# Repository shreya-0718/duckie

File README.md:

# duckie!

Hello! Welcome to my first PCB, powered by Solder!

My slack username: @shreyaluu

This is just a little duck keychain whose eyes light up when the button is pressed. It also buzzes, and the "buzz level" is adjustable with the potentiometer!

### Bill of Materials
- 1x PCB
- 1x 3V Battery
- 2x LEDs
- 2x 220 Ohm Resistor
- 1x Battery Holder
- 1x Vibration Motor
- 1x Potentiometer

### Screenshots :)

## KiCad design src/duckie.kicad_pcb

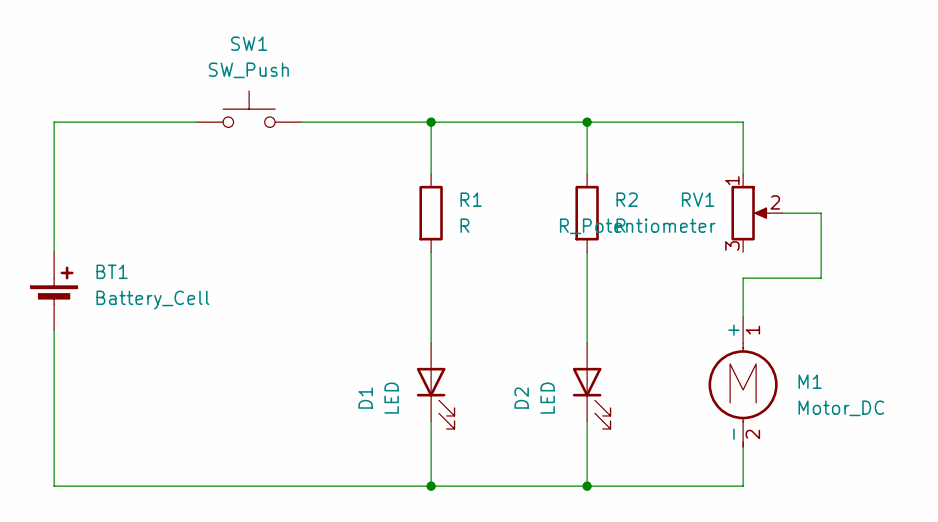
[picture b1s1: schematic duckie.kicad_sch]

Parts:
BT1: Battery_Cell; BatteryHolder_Keystone_3034_1x20mm
D1, D2: LED; LED_D5.0mm
M1: Motor_DC; PinHeader_1x02_P2.54mm_Vertical
R1, R2: R; R_Axial_DIN0207_L6.3mm_D2.5mm_P7.62mm_Horizontal
RV1: R_Potentiometer; Potentiometer_Vishay_T73YP_Vertical
SW1: SW_Push; SW_PUSH_6mm

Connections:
unnamed: BT1.1 (+), SW1.1
unnamed: BT1.2 (-), D1.1 (K), D2.1 (K), M1.2 (-)
unnamed: D1.2 (A), R1.2
unnamed: D2.2 (A), R2.2
unnamed: M1.1 (+), RV1.2
unnamed: R1.1, R2.1, RV1.1, SW1.2

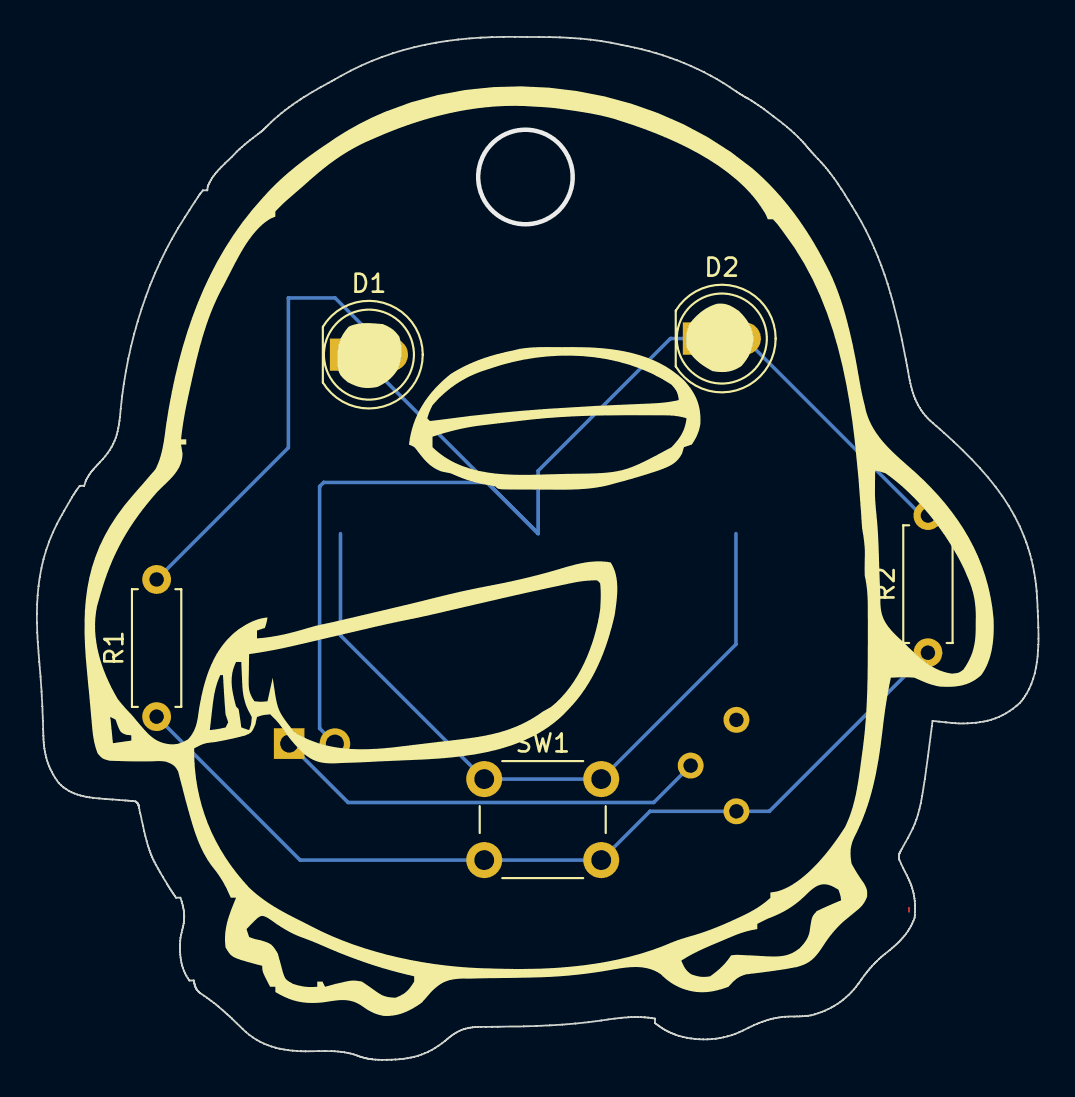
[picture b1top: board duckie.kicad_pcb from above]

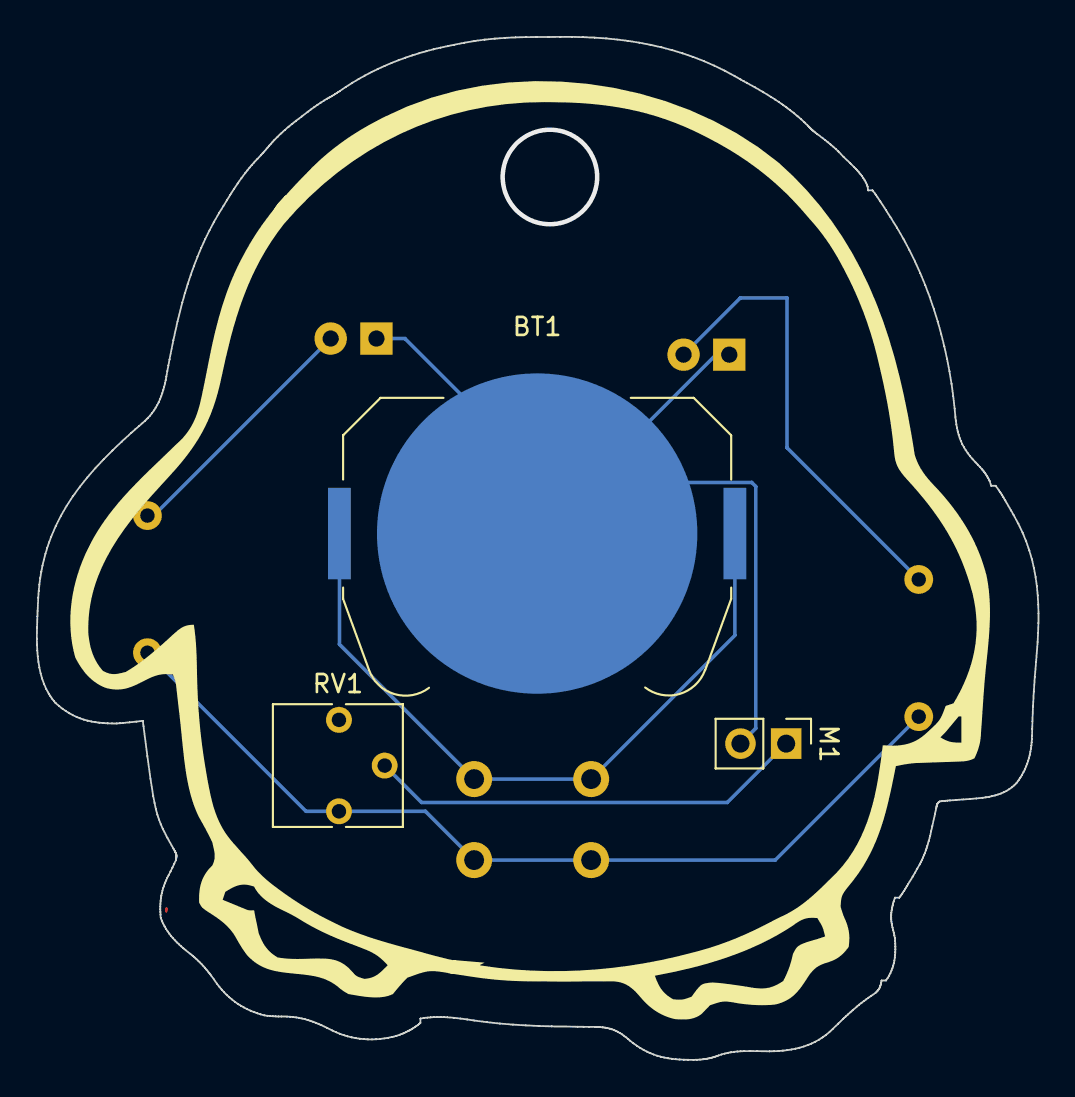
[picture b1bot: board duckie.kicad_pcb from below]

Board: 2 copper layers, 55.6 x 56.8 mm, 8 parts (3 on the bottom side), 6 nets.

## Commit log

2025-06-17 uploaded Kicad files
2025-06-17 added "src" folder
2025-06-19 Updated PCB with buzz motor and potentiometer, and updated JOURNAL.md
2025-06-19 Updated README.md and JOURNAL.md
2025-06-19 Update README.md
    Fixed image url for final front of the pcb model
2025-06-19 Changing potentiometer wiring
